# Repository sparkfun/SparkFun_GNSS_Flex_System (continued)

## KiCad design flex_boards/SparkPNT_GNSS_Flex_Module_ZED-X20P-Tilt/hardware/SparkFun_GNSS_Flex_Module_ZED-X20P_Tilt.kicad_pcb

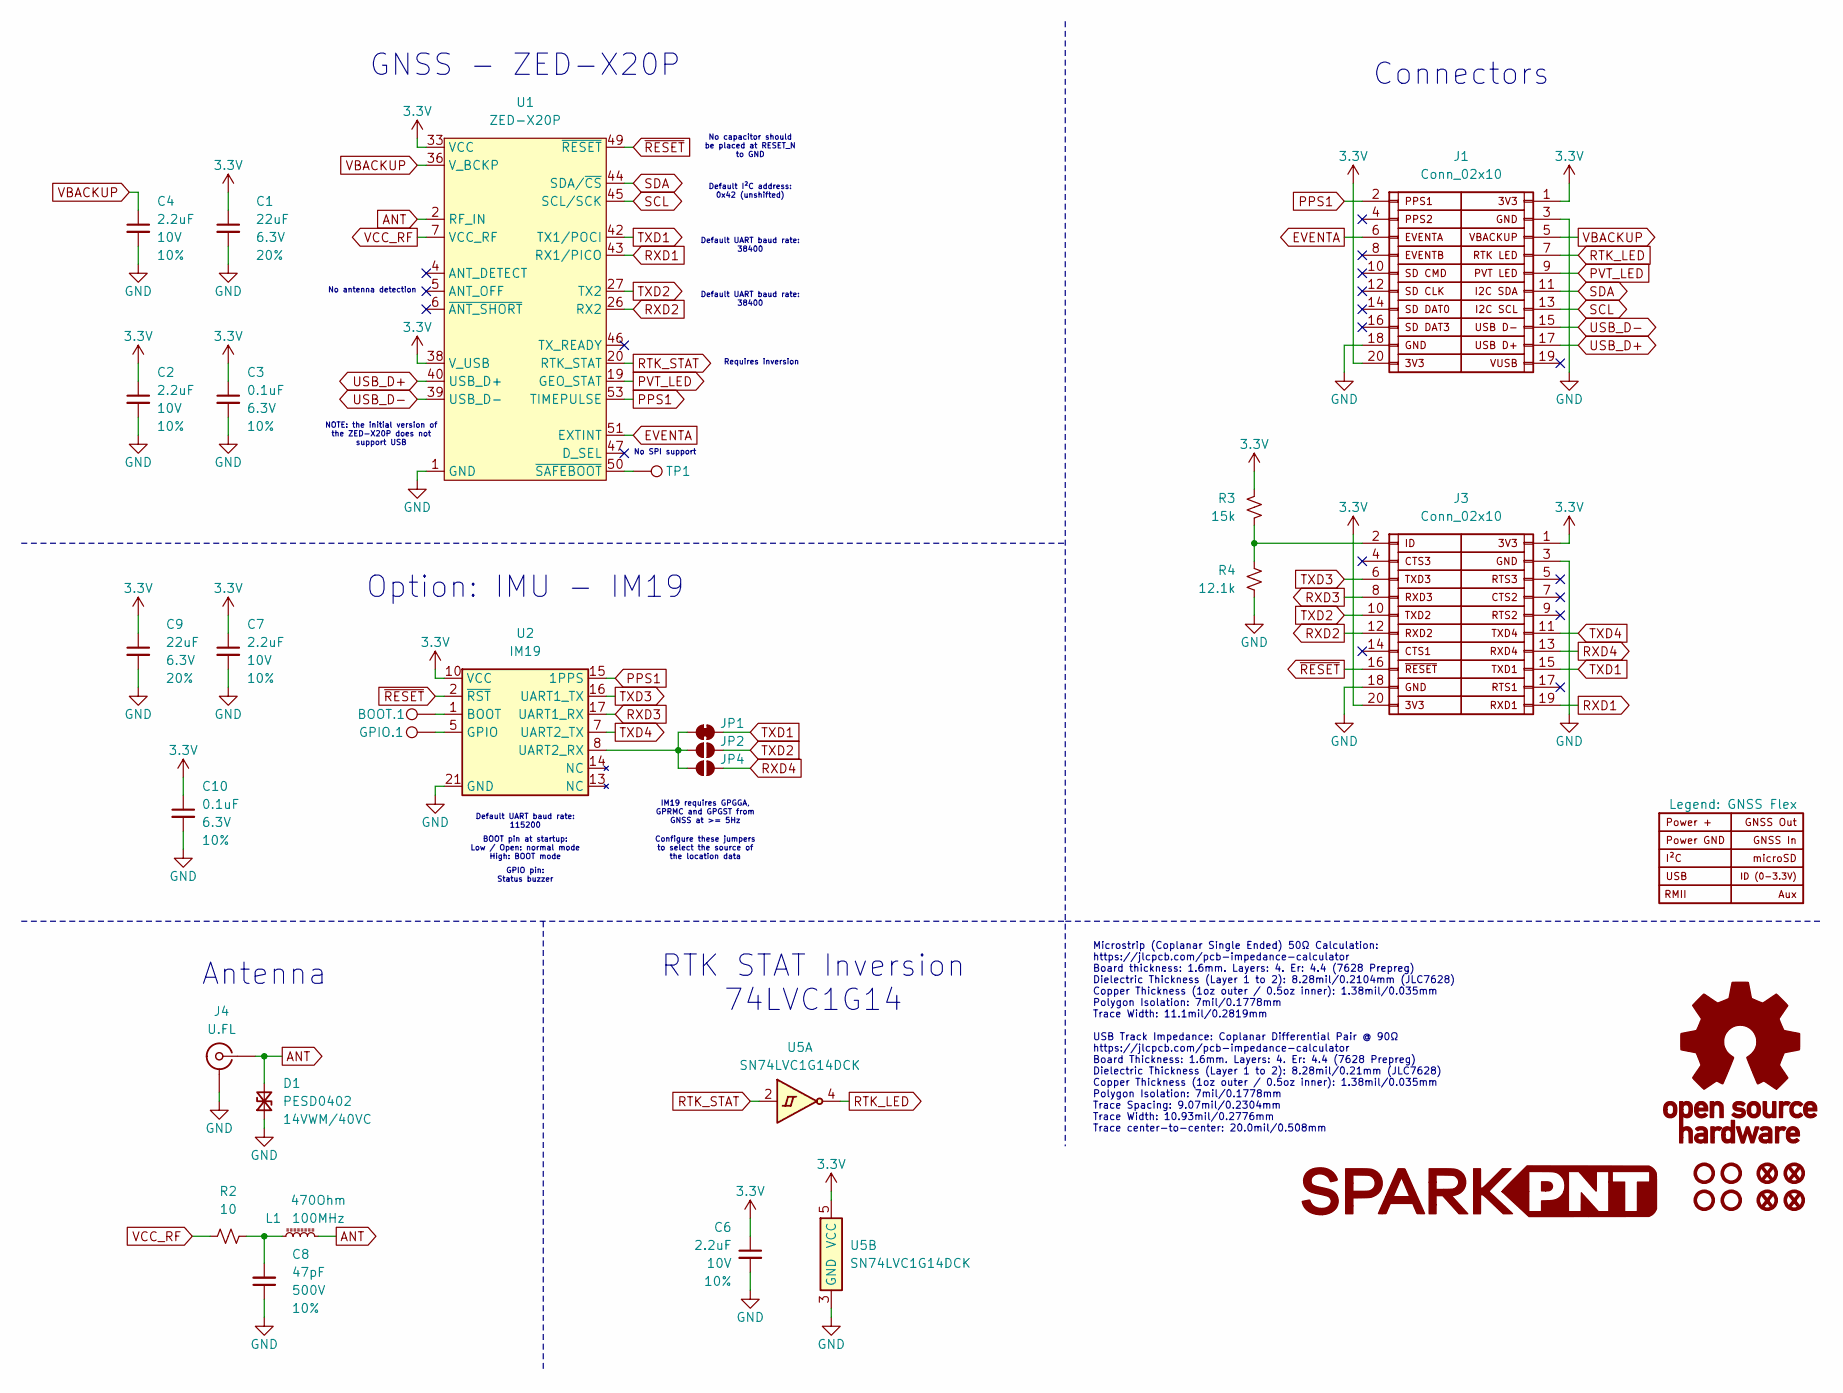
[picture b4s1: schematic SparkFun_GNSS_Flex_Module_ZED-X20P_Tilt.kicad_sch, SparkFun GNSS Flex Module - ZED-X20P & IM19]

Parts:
BOOT.1: 1.0mm; TestPoint-1.0mm
C1, C9: 22uF; C_0603_1608Metric; Voltage 6.3V; Tolerance 20%
C2, C4, C6, C7: 2.2uF; C_0402_1005Metric; Voltage 10V; Tolerance 10%
C3, C10: 0.1uF; C_0402_1005Metric; Voltage 6.3V; Tolerance 10%
C8: 47pF; C_0402_1005Metric; Voltage 500V; Tolerance 10%
D1: PESD0402; C_0402_1005Metric; Rating 14VWM/40VC
FID1, FID2, FID3, FID4: Fiducial_0.5mm; Fiducial_0.5mm_Mask1mm
G1: LOGO
G3: OSHW_Logo; Creative_Commons_License
GPIO.1: 1.0mm; TestPoint-1.0mm
J1, J3: Conn_02x10; 2x10_P2.0mm_Socket_Vertical_SMD_Pegs
J2: Legend: GNSS Flex; GNSS_Flex_Template
J4: U.FL
JP1: Jumper_2_NC_Trace
JP2, JP4: Jumper_2_NO
L1: 470Ohm; C_0603_1608Metric
R2: 10; R_0402_1005Metric
R3: 15k; R_0603_1608Metric
R4: 12.1k; R_0603_1608Metric
ST1, ST2, ST3, ST4: Standoff
TP1: 1.0mm; TestPoint-1.0mm
U1: ZED-X20P; ZED-F9P_F9T_F9R_X20P
U2: IM19
U5: SN74LVC1G14DCK; SOT-353

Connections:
3.3V: C1.1, C2.1, C3.1, C6.1, C7.1, C9.1, C10.1, J1.1, J1.20, J3.1, J3.20, R3.2, U1.33 (VCC), U1.34 (VCC), U1.38 (V_USB), U2.6 (VCC), U2.10 (VCC), U5.5 (VCC)
ANT: D1.2 (A2), J4.1 (In), L1.2, U1.2 (RF_IN)
EVENTA: J1.6, U1.51 (EXTINT)
GND: C1.2, C2.2, C3.2, C4.2, C6.2, C7.2, C8.1, C9.2, C10.2, D1.1 (A1), J1.3, J1.18, J3.3, J3.18, J4.2 (Ext), R4.1, U1.1 (GND), U1.3 (GND), U1.12 (GND), U1.14 (GND), U1.32 (GND), U1.37 (GND), U1.41 (GND), U1.48 (GND), U1.55 (GND), U1.56 (GND), U1.57 (GND), U1.58 (GND), U1.59 (GND), U1.60 (GND), U1.61 (GND), U1.62 (GND), U1.63 (GND), U1.64 (GND), U1.65 (GND), U1.66 (GND), U1.67 (GND), U1.68 (GND), U1.69 (GND), U1.70 (GND), U1.71 (GND), U1.72 (GND), U1.73 (GND), U1.74 (GND), U1.75 (GND), U1.76 (GND), U1.77 (GND), U1.78 (GND), U1.79 (GND), U1.80 (GND), U1.81 (GND), U1.82 (GND), U1.83 (GND), U1.84 (GND), U1.85 (GND), U1.86 (GND), U1.87 (GND), U1.88 (GND), U1.89 (GND), U1.90 (GND), U1.91 (GND), U1.92 (GND), U1.93 (GND), U1.94 (GND), U1.95 (GND), U1.96 (GND), U1.97 (GND), U1.98 (GND), U1.99 (GND), U1.100 (GND), U1.101 (GND), U1.102 (GND), U2.3 (GND), U2.4 (GND), U2.9 (GND), U2.18 (GND), U2.21 (GND), U5.3 (GND)
unnamed: C8.2, L1.1, R2.2
unnamed: J3.2, R3.1, R4.2
unnamed: JP1.1 (A), JP2.1 (A), JP4.1 (A), U2.8 (UART2_RX)
unnamed: TP1.1, U1.50 (~SAFEBOOT)
unnamed: BOOT.1.1, U2.1 (BOOT)
unnamed: GPIO.1.1, U2.5 (GPIO)
PPS1: J1.2, U1.53 (TIMEPULSE), U2.15 (1PPS)
PVT_LED: J1.9, U1.19 (GEO_STAT)
RTK_LED: J1.7, U5.4
RTK_STAT: U1.20 (RTK_STAT), U5.2
RXD1: J3.19, U1.43 (RX1/PICO)
RXD2: J3.12, U1.26 (RX2)
RXD3: J3.8, U2.17 (UART1_RX)
RXD4: J3.13, JP4.2 (B)
SCL: J1.13, U1.45 (SCL/SCK)
SDA: J1.11, U1.44 (SDA/~CS)
TXD1: J3.15, JP1.2 (B), U1.42 (TX1/POCI)
TXD2: J3.10, JP2.2 (B), U1.27 (TX2)
TXD3: J3.6, U2.16 (UART1_TX)
TXD4: J3.11, U2.7 (UART2_TX)
USB_D+: J1.17, U1.40 (USB_D+)
USB_D-: J1.15, U1.39 (USB_D-)
VBACKUP: C4.1, J1.5, U1.36 (V_BCKP)
VCC_RF: R2.1, U1.7 (VCC_RF)
~RESET: J3.16, U1.49 (~RESET), U2.2 (~RST)

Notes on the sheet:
Configure these jumpers to select the source of the location data
Option: IMU - IM19
IM19 requires GPGGA, GPRMC and GPGST from GNSS at >= 5Hz
Antenna
NOTE: the initial version of the ZED-X20P does not support USB
GPIO pin: Status buzzer
No antenna detection
Connectors
Default UART baud rate: 38400
Default I²C address: 0x42 (unshifted)
Requires inversion
GNSS - ZED-X20P
BOOT pin at startup: Low / Open: normal mode High: BOOT mode
No SPI support
Default UART baud rate: 115200
No capacitor should be placed at RESET_N to GND
Microstrip (Coplanar Single Ended) 50Ω Calculation: https://jlcpcb.com/pcb-impedance-calculator Board thickness: 1.6mm. Layers: 4. Er: 4.4 (7628 Prepreg) Dielectric Thickness (Layer 1 to 2): 8.28mil/0.2104mm (JLC7628) Copper Thickness (1oz outer / 0.5oz inner): 1.38mil/0.035mm Polygon Isolation: 7m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
RTK STAT Inversion 74LVC1G14

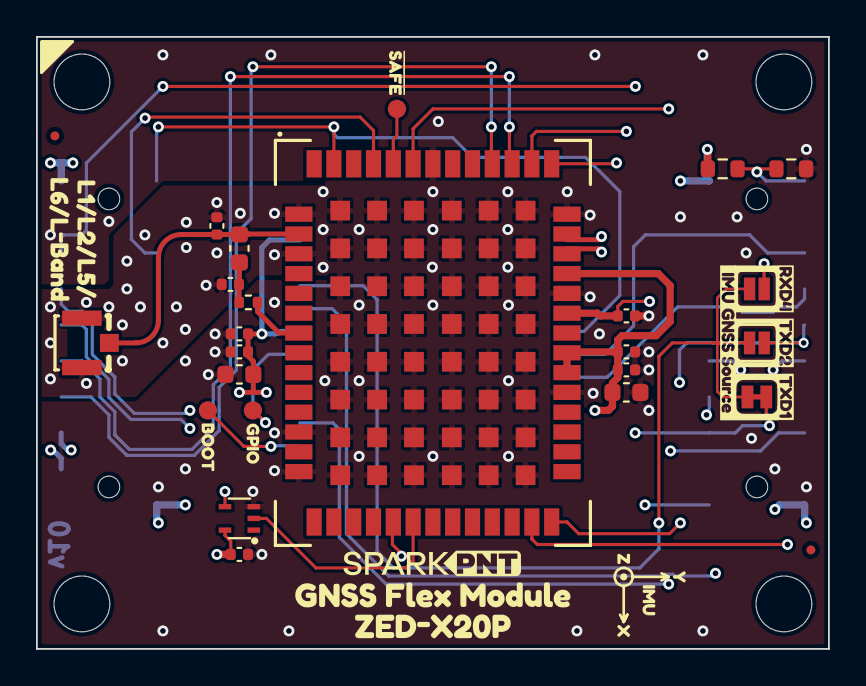
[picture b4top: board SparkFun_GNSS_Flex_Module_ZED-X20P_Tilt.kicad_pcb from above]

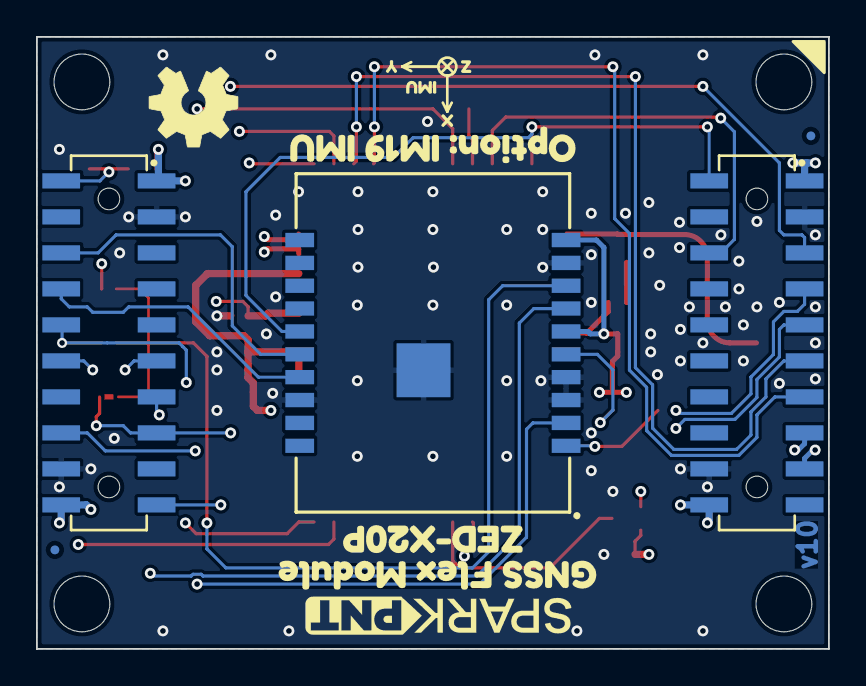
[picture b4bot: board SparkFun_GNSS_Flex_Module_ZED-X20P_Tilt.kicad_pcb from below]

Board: 4 copper layers, 44.0 x 34.0 mm, 59 parts (13 on the bottom side), 29 nets.

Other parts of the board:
Ref**: Val**; OSHW_Logo_5mm
kibuzzard-67E28C2D: G***; kibuzzard-67E28C2D
kibuzzard-67E2880B: G***; kibuzzard-67E2880B
kibuzzard-67F7F23B: G***; kibuzzard-67F7F23B
kibuzzard-67F7F255: G***; kibuzzard-67F7F255
kibuzzard-67FE65EC: G***; kibuzzard-67FE65EC
kibuzzard-67FE65FA: G***; kibuzzard-67FE65FA
kibuzzard-67FE650E: G***; kibuzzard-67FE650E
kibuzzard-67FFA928, kibuzzard-67FFA928#2: G***; kibuzzard-67FFA928
kibuzzard-67FFB45E, kibuzzard-67FFB45E#2: G***; kibuzzard-67FFB45E
kibuzzard-67FFB46A, kibuzzard-67FFB46A#2: G***; kibuzzard-67FFB46A
kibuzzard-67FFB450, kibuzzard-67FFB450#2: G***; kibuzzard-67FFB450
kibuzzard-682DAEE5: G***; kibuzzard-682DAEE5
kibuzzard-682DAFF9: G***; kibuzzard-682DAFF9
kibuzzard-682DB02A: G***; kibuzzard-682DB02A
kibuzzard-68261DE3: G***; kibuzzard-68261DE3
kibuzzard-68261E9D: G***; kibuzzard-68261E9D
kibuzzard-68261F64: G***; kibuzzard-68261F64
kibuzzard-68261F97: G***; kibuzzard-68261F97

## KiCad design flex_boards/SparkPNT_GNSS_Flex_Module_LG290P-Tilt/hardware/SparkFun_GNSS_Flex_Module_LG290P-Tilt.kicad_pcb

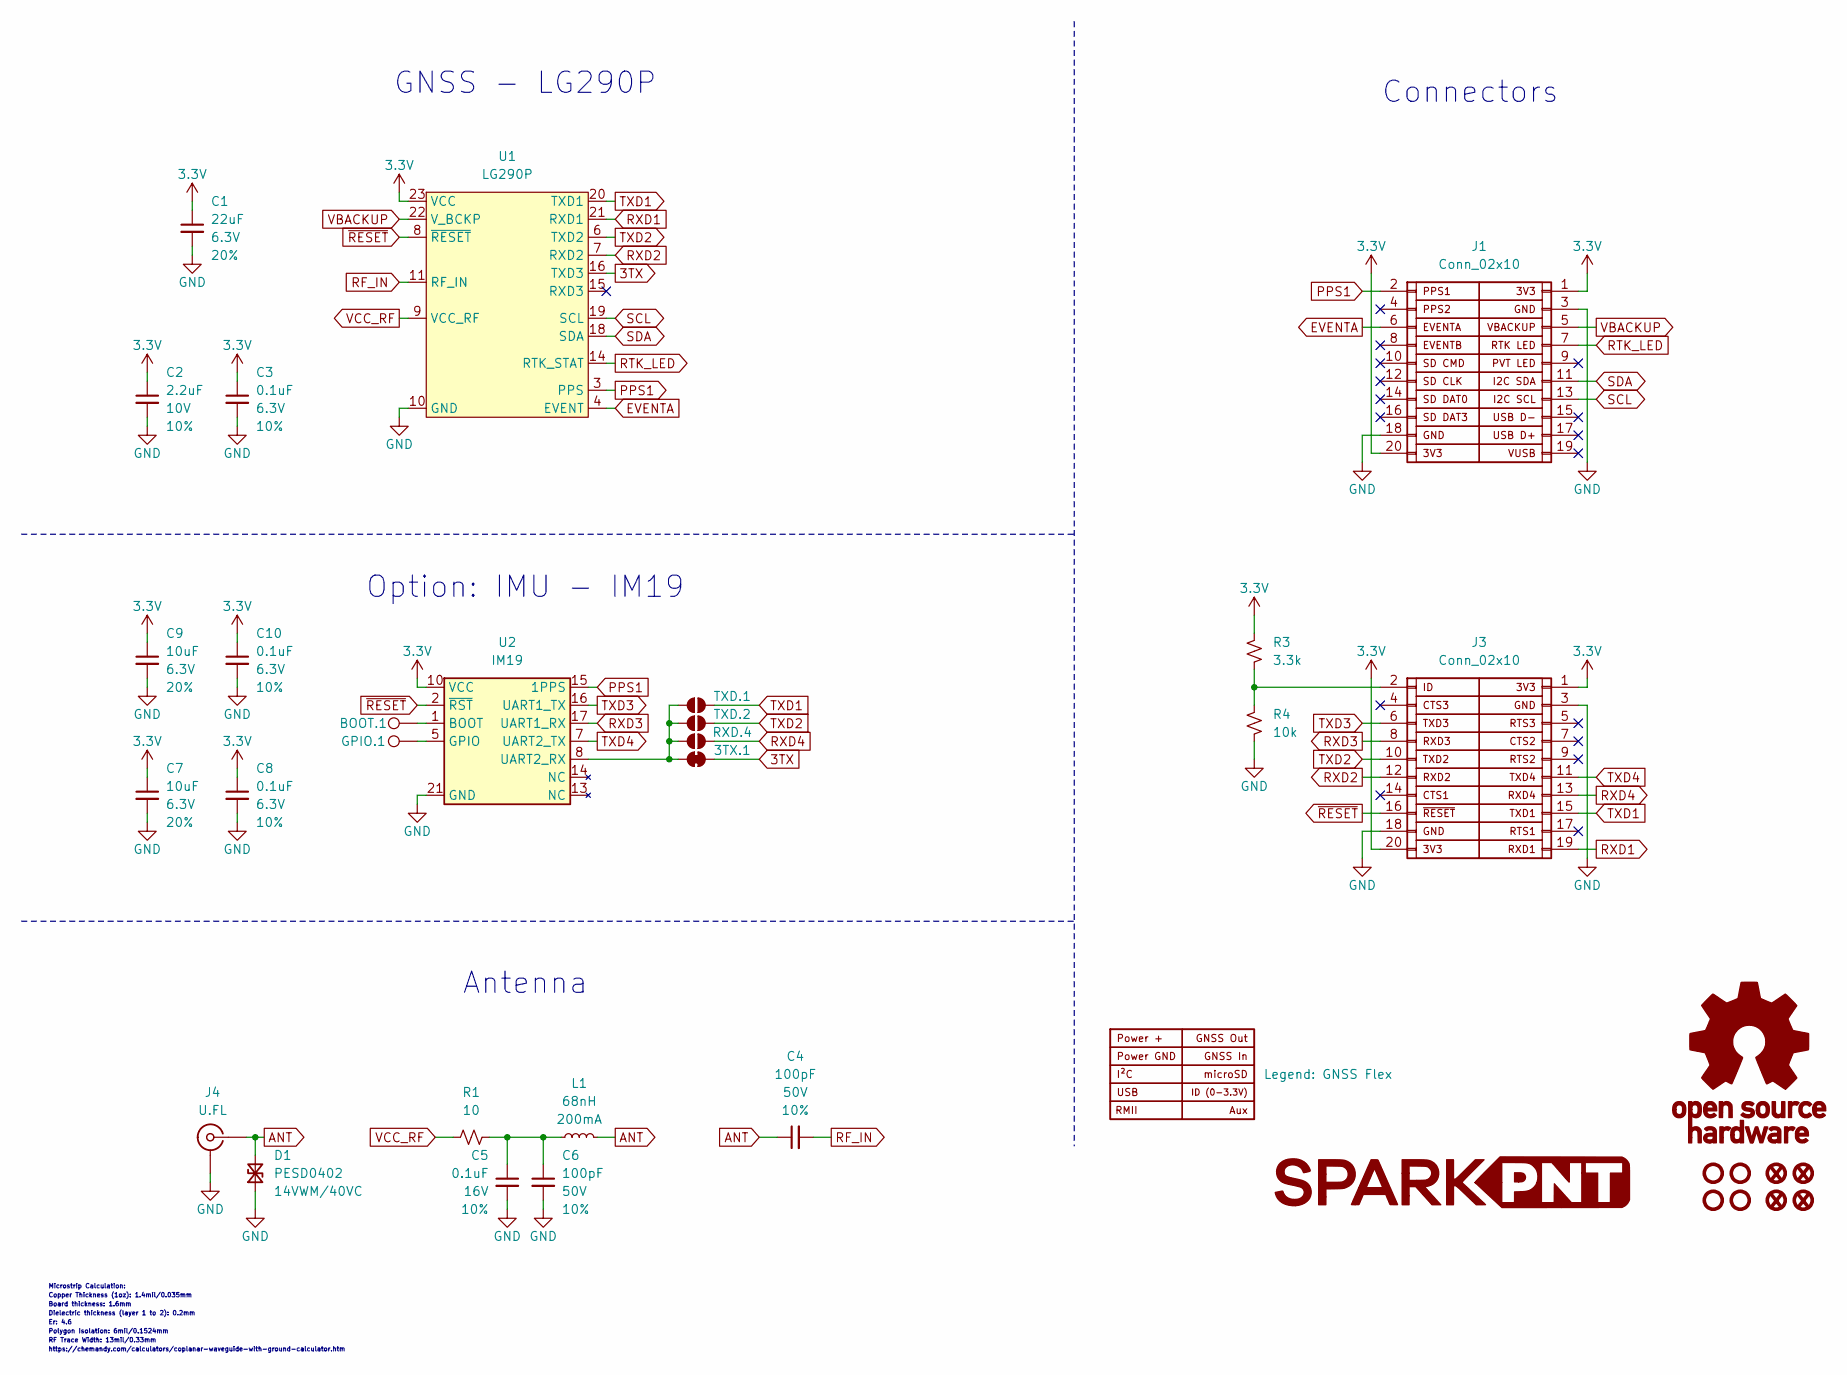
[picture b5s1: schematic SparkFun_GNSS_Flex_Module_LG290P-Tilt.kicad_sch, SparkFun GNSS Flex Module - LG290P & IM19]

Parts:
3TX.1: Jumper_2_NC_Trace
BOOT.1: 1.0mm; TestPoint-1.0mm
C1: 22uF; C_0603_1608Metric; Voltage 6.3V; Tolerance 20%
C2: 2.2uF; C_0402_1005Metric; Voltage 10V; Tolerance 10%
C3, C8, C10: 0.1uF; C_0402_1005Metric; Voltage 6.3V; Tolerance 10%
C4, C6: 100pF; C_0402_1005Metric; Voltage 50V; Tolerance 10%
C5: 0.1uF; C_0402_1005Metric; Voltage 16V; Tolerance 10%
C7, C9: 10uF; C_0603_1608Metric; Voltage 6.3V; Tolerance 20%
D1: PESD0402; C_0402_1005Metric; Rating 14VWM/40VC
FID1, FID2, FID3, FID4: Fiducial_0.5mm; Fiducial_0.5mm_Mask1mm
G1: LOGO
G3: OSHW_Logo; Creative_Commons_License
GPIO.1: 1.0mm; TestPoint-1.0mm
J1, J3: Conn_02x10; 2x10_P2.0mm_Socket_Vertical_SMD_Pegs
J2: Legend: GNSS Flex; GNSS_Flex_Template
J4: U.FL
L1: 68nH; C_0402_1005Metric
R1: 10; R_0402_1005Metric
R3: 3.3k; R_0603_1608Metric
R4: 10k; R_0603_1608Metric
RXD.4: Jumper_2_NO
ST1, ST2, ST3, ST4: Standoff
TXD.1, TXD.2: Jumper_2_NO
U1: LG290P; Quectel_LG290P
U2: IM19

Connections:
3.3V: C1.1, C2.1, C3.1, C7.1, C8.1, C9.1, C10.1, J1.1, J1.20, J3.1, J3.20, R3.2, U1.23 (VCC), U2.6 (VCC), U2.10 (VCC)
3TX: 3TX.1.2 (B), U1.16 (TXD3)
ANT: C4.1, D1.2 (A2), J4.1 (In), L1.2
EVENTA: J1.6, U1.4 (EVENT)
GND: C1.2, C2.2, C3.2, C5.2, C6.2, C7.2, C8.2, C9.2, C10.2, D1.1 (A1), J1.3, J1.18, J3.3, J3.18, J4.2 (Ext), R4.1, U1.10 (GND), U1.12 (GND), U1.13 (GND), U1.24 (GND), U1.25 (GND), U2.3 (GND), U2.4 (GND), U2.9 (GND), U2.18 (GND), U2.21 (GND)
unnamed: 3TX.1.1 (A), RXD.4.1 (A), TXD.1.1 (A), TXD.2.1 (A), U2.8 (UART2_RX)
unnamed: C5.1, C6.1, L1.1, R1.2
unnamed: J3.2, R3.1, R4.2
unnamed: BOOT.1.1, U2.1 (BOOT)
unnamed: GPIO.1.1, U2.5 (GPIO)
PPS1: J1.2, U1.3 (PPS), U2.15 (1PPS)
RF_IN: C4.2, U1.11 (RF_IN)
RTK_LED: J1.7, U1.14 (RTK_STAT)
RXD1: J3.19, U1.21 (RXD1)
RXD2: J3.12, U1.7 (RXD2)
RXD3: J3.8, U2.17 (UART1_RX)
RXD4: J3.13, RXD.4.2 (B)
SCL: J1.13, U1.19 (SCL)
SDA: J1.11, U1.18 (SDA)
TXD1: J3.15, TXD.1.2 (B), U1.20 (TXD1)
TXD2: J3.10, TXD.2.2 (B), U1.6 (TXD2)
TXD3: J3.6, U2.16 (UART1_TX)
TXD4: J3.11, U2.7 (UART2_TX)
VBACKUP: J1.5, U1.22 (V_BCKP)
VCC_RF: R1.1, U1.9 (VCC_RF)
~RESET: J3.16, U1.8 (~RESET), U2.2 (~RST)

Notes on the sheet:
Copper Thickness (1oz): 1.4mil/0.035mm
Board thickness: 1.6mm
Er: 4.6
Antenna
Option: IMU - IM19
Connectors
GNSS - LG290P
https://chemandy.com/calculators/coplanar-waveguide-with-ground-calculator.htm
Microstrip Calculation:
Polygon Isolation: 6mil/0.1524mm
Dielectric thickness (layer 1 to 2): 0.2mm
RF Trace Width: 13mil/0.33mm

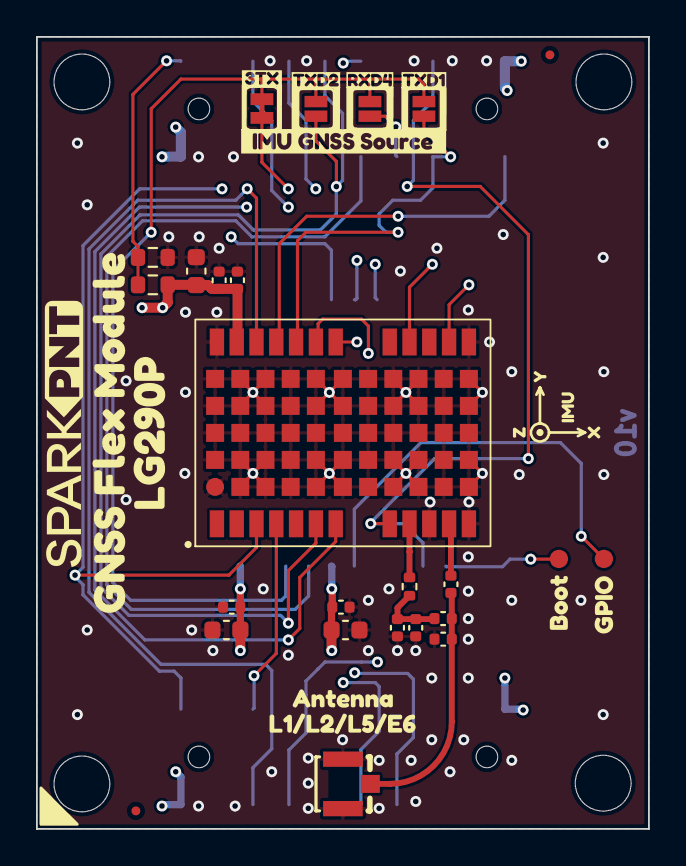
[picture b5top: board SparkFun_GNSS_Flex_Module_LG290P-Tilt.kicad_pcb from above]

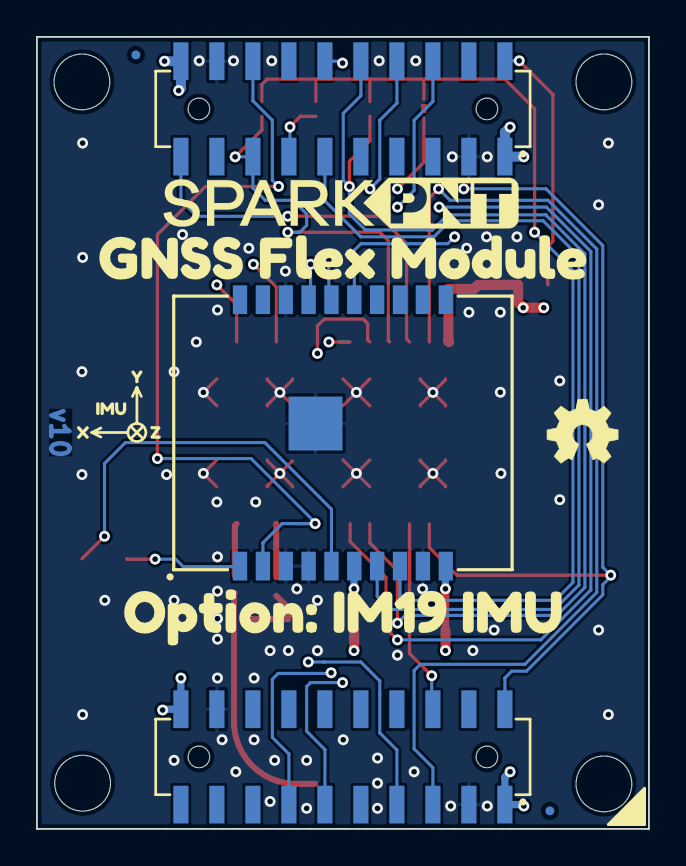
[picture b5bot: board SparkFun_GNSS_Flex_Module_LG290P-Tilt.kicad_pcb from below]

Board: 4 copper layers, 34.0 x 44.0 mm, 58 parts (12 on the bottom side), 26 nets.

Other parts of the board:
Ref**: Val**; OSHW_Logo_4mm
kibuzzard-67DC4CF4: G***; kibuzzard-67DC4CF4
kibuzzard-67DC4D0C: G***; kibuzzard-67DC4D0C
kibuzzard-67FFA928, kibuzzard-67FFA928#2: G***; kibuzzard-67FFA928
kibuzzard-67FFB45E, kibuzzard-67FFB45E#2: G***; kibuzzard-67FFB45E
kibuzzard-67FFB46A, kibuzzard-67FFB46A#2: G***; kibuzzard-67FFB46A
kibuzzard-67FFB450, kibuzzard-67FFB450#2: G***; kibuzzard-67FFB450
kibuzzard-679B60B6: G***; kibuzzard-679B60B6
kibuzzard-684984CE: G***; kibuzzard-684984CE
kibuzzard-684984F2: G***; kibuzzard-684984F2
kibuzzard-6849609B: G***; kibuzzard-6849609B
kibuzzard-6849850D: G***; kibuzzard-6849850D
kibuzzard-67975357: G***; kibuzzard-67975357
kibuzzard-67975369: G***; kibuzzard-67975369
kibuzzard-68496623: G***; kibuzzard-68496623
kibuzzard-68496634: G***; kibuzzard-68496634
kibuzzard-68498826: G***; kibuzzard-68498826
kibuzzard-68498864: G***; kibuzzard-68498864

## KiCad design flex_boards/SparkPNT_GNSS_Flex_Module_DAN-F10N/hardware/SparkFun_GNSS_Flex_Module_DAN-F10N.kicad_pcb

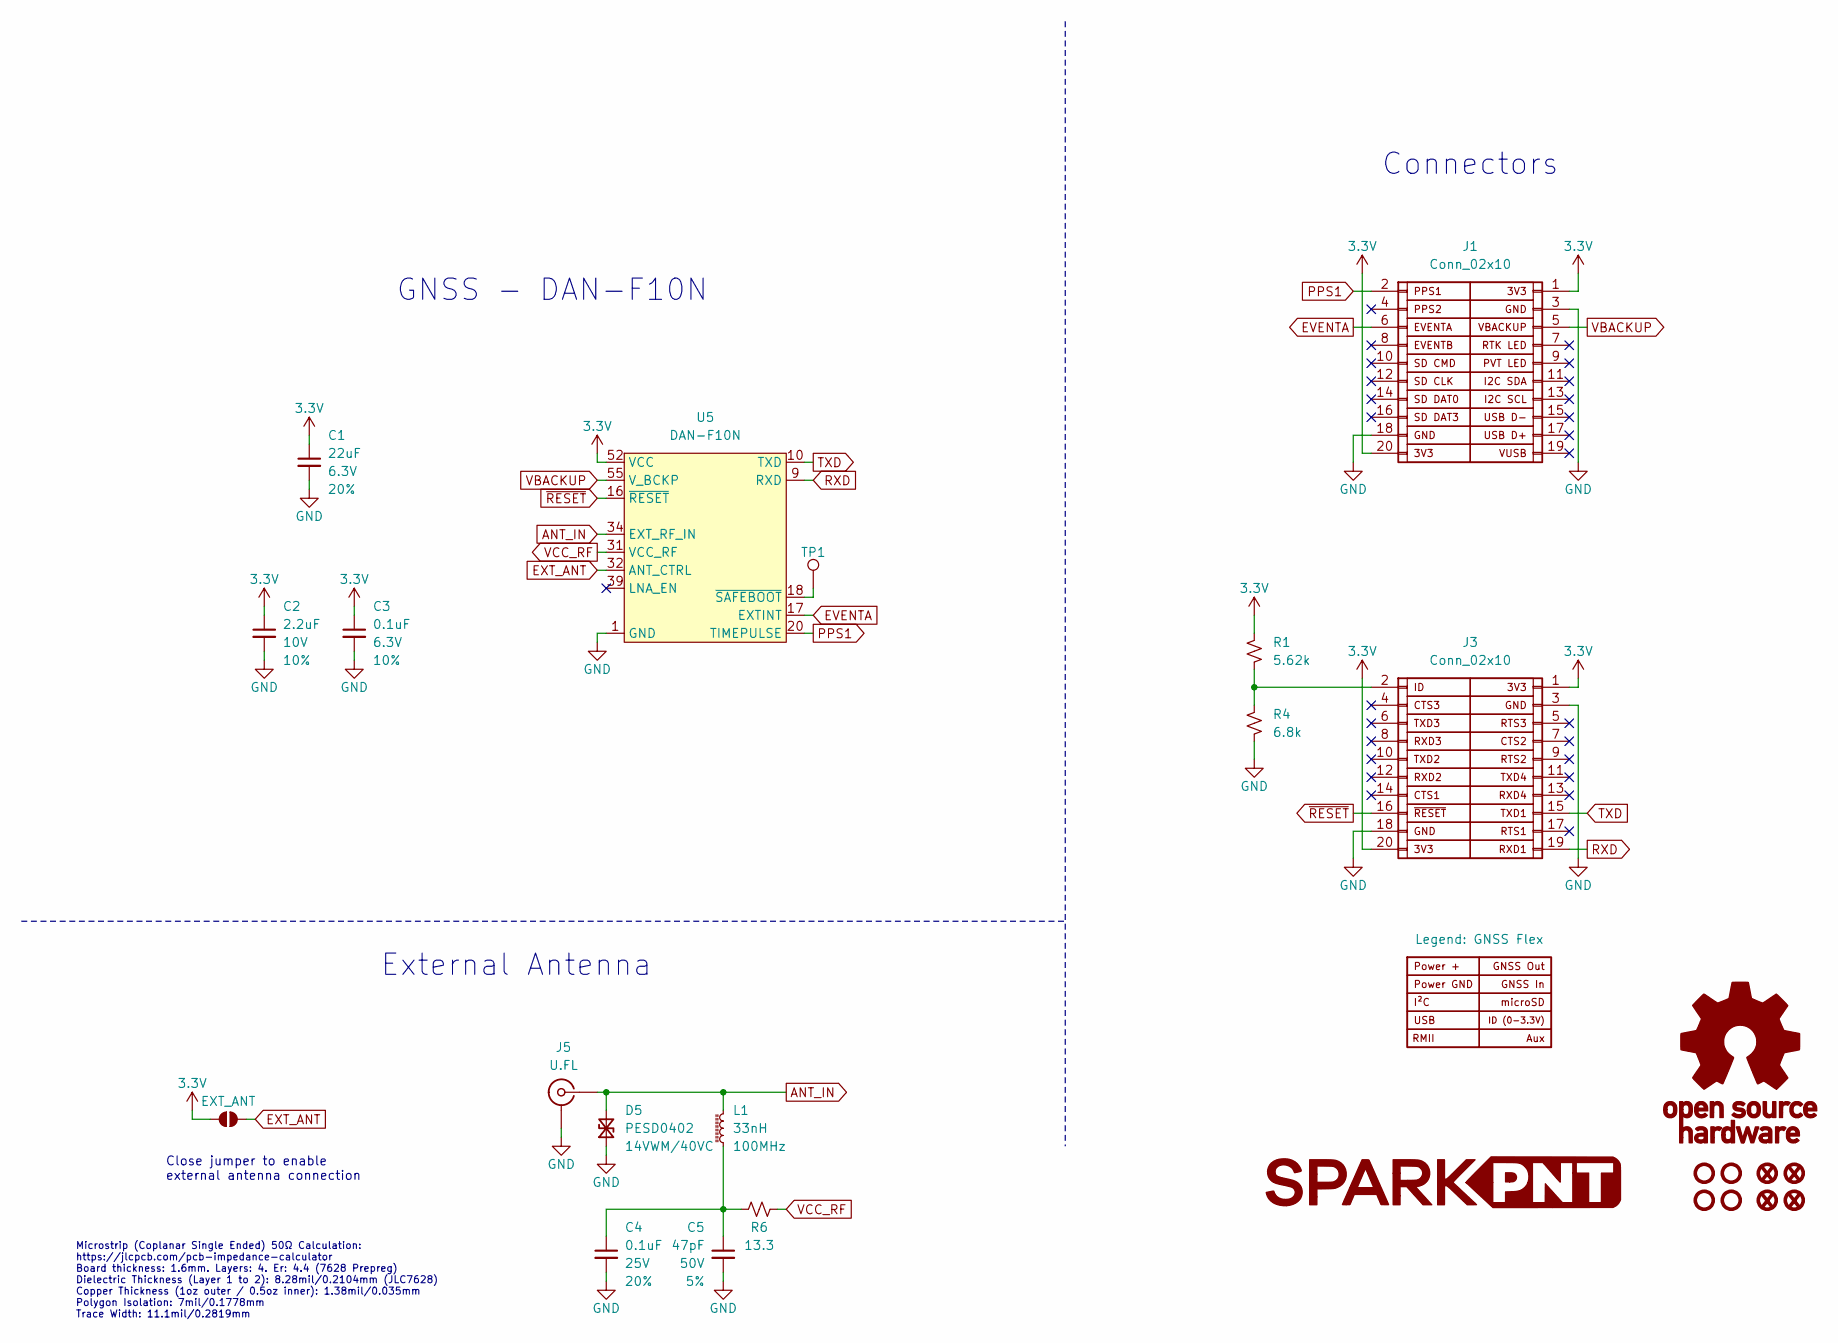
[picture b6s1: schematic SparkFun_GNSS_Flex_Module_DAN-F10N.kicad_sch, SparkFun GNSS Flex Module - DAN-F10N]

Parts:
C1: 22uF; C_0603_1608Metric; Voltage 6.3V; Tolerance 20%
C2: 2.2uF; C_0402_1005Metric; Voltage 10V; Tolerance 10%
C3: 0.1uF; C_0402_1005Metric; Voltage 6.3V; Tolerance 10%
C4: 0.1uF; C_0603_1608Metric; Voltage 25V; Tolerance 20%
C5: 47pF; C_0603_1608Metric; Voltage 50V; Tolerance 5%
D5: PESD0402; C_0402_1005Metric; Rating 14VWM/40VC
FID1, FID2, FID3, FID4: Fiducial_0.5mm; Fiducial_0.5mm_Mask1mm
G1: LOGO
G3: OSHW_Logo; Creative_Commons_License
J1, J3: Conn_02x10; 2x10_2.0mm_Female_Socket_Vertical_SMD_Pegs
J2: Legend: GNSS Flex; GNSS_Flex_Template
J5: U.FL
JP1: EXT_ANT; Jumper_2_NO
L1: 33nH; C_0603_1608Metric
R1: 5.62k; R_0603_1608Metric
R4: 6.8k; R_0603_1608Metric
R6: 13.3; R_2512_6332Metric
ST1, ST2, ST3, ST4: Standoff
TP1: 1.0mm; TestPoint-1.0mm
U5: DAN-F10N

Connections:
3.3V: C1.1, C2.1, C3.1, J1.1, J1.20, J3.1, J3.20, JP1.1 (A), R1.2, U5.52 (VCC), U5.53 (VCC)
ANT_IN: D5.2 (A2), J5.1 (In), L1.2, U5.34 (EXT_RF_IN)
EVENTA: J1.6, U5.17 (EXTINT)
EXT_ANT: JP1.2 (B), U5.32 (ANT_CTRL)
GND: C1.2, C2.2, C3.2, C4.2, C5.2, D5.1 (A1), J1.3, J1.18, J3.3, J3.18, J5.2 (Ext), R4.1, U5.1 (GND), U5.2 (GND), U5.3 (GND), U5.4 (GND), U5.5 (GND), U5.6 (GND), U5.7 (GND), U5.8 (GND), U5.13 (GND), U5.14 (GND), U5.15 (GND), U5.19 (GND), U5.21 (GND), U5.22 (GND), U5.23 (GND), U5.26 (GND), U5.27 (GND), U5.28 (GND), U5.29 (GND), U5.30 (GND), U5.33 (GND), U5.35 (GND), U5.37 (GND), U5.38 (GND), U5.40 (GND), U5.41 (GND), U5.42 (GND), U5.43 (GND), U5.44 (GND), U5.47 (GND), U5.48 (GND), U5.49 (GND), U5.50 (GND), U5.51 (GND), U5.54 (GND), U5.56 (GND), U5.57 (GND)
unnamed: C4.1, C5.1, L1.1, R6.2
unnamed: J3.2, R1.1, R4.2
unnamed: TP1.1, U5.18 (~SAFEBOOT)
PPS1: J1.2, U5.20 (TIMEPULSE)
RXD: J3.19, U5.9 (RXD)
TXD: J3.15, U5.10 (TXD)
VBACKUP: J1.5, U5.55 (V_BCKP)
VCC_RF: R6.1, U5.31 (VCC_RF)
~RESET: J3.16, U5.16 (~RESET)

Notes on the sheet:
External Antenna
Connectors
GNSS - DAN-F10N
Close jumper to enable external antenna connection
Microstrip (Coplanar Single Ended) 50Ω Calculation: https://jlcpcb.com/pcb-impedance-calculator Board thickness: 1.6mm. Layers: 4. Er: 4.4 (7628 Prepreg) Dielectric Thickness (Layer 1 to 2): 8.28mil/0.2104mm (JLC7628) Copper Thickness (1oz outer / 0.5oz inner): 1.38mil/0.035mm Polygon Isolation: 7m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

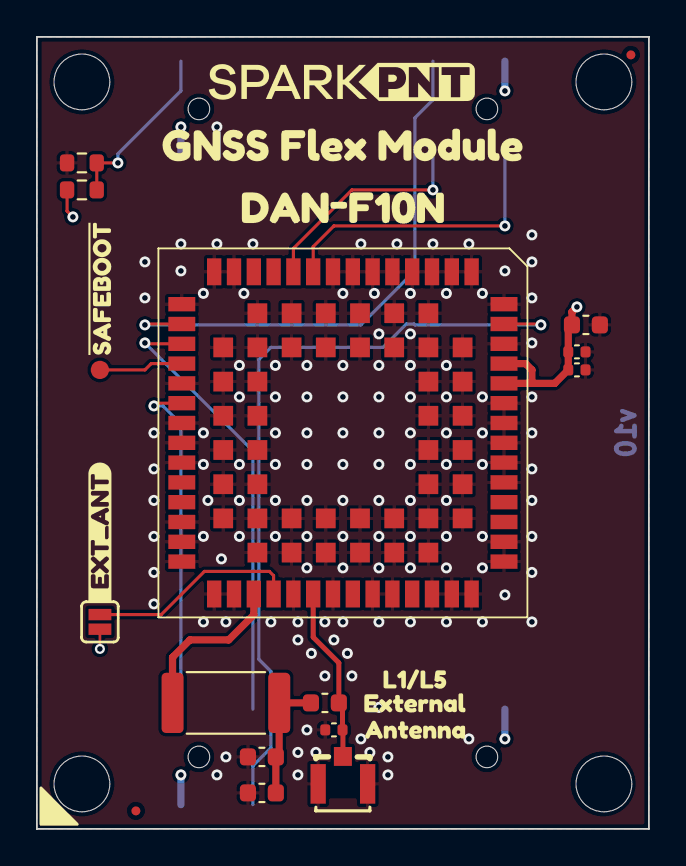
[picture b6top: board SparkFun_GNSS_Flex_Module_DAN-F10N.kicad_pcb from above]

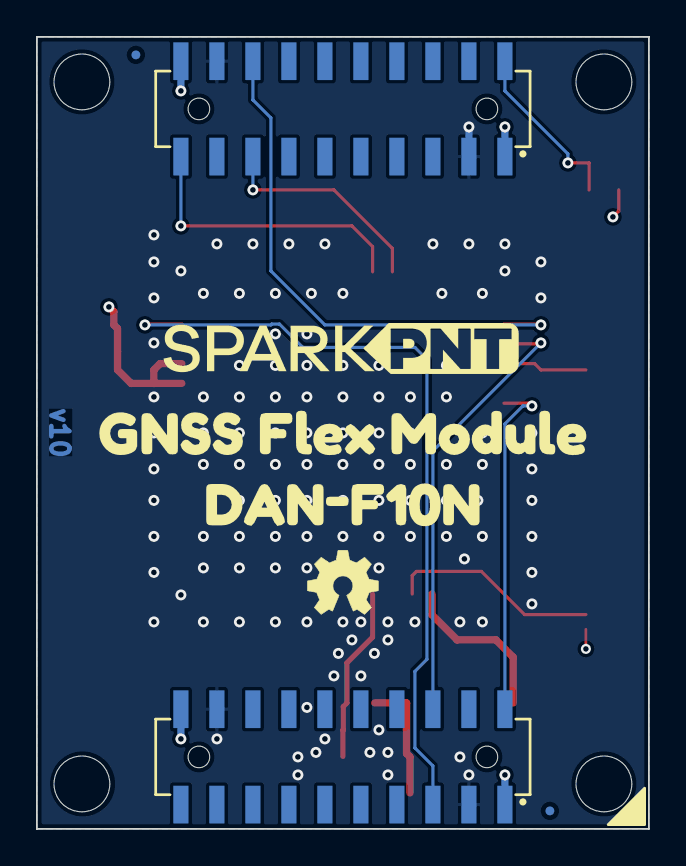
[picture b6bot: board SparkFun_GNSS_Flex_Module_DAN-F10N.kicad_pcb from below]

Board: 4 copper layers, 34.0 x 44.0 mm, 36 parts (7 on the bottom side), 14 nets.

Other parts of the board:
Ref**: Val**; OSHW_Logo_4mm
kibuzzard-67DC4CF4: G***; kibuzzard-67DC4CF4
kibuzzard-67DC4D0C: G***; kibuzzard-67DC4D0C
kibuzzard-67F5D276: G***; kibuzzard-67F5D276
kibuzzard-67F49BA9: G***; kibuzzard-67F49BA9
kibuzzard-67F49BB0: G***; kibuzzard-67F49BB0
kibuzzard-67F49BC0: G***; kibuzzard-67F49BC0
kibuzzard-67FE95EA: G***; kibuzzard-67FE95EA
kibuzzard-67FE959B: G***; kibuzzard-67FE959B
kibuzzard-67975369: G***; kibuzzard-67975369

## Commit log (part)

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2025-04-29 Remove directories
2025-04-29 Update template files
2025-05-15 Initial Draft - Flex System
2025-05-15 Initial Draft - mosaic-X5
2025-05-16 Update - mosaic-X5
    - Adds QR codes for videos
    - Fix typos
2025-05-16 Update - Flex System
    - Fix link
2025-05-16 Add build workflow
    Add workflow to build documentation for GitHub Pages
2025-05-16 Deployed fa99f3e with MkDocs version: 1.6.1
2025-05-16 Remove file
2025-05-16 Deployed a7084e1 with MkDocs version: 1.6.1
2025-05-16 Deployed c31044d with MkDocs version: 1.6.1
2025-05-16 Manually add pHAT Files
2025-05-16 Deployed fc5b3ee with MkDocs version: 1.6.1
2025-05-19 Minor corrections
2025-05-19 Correct X5 grid
2025-05-19 Correct image link
2025-05-19 Fix path to pHAT files
2025-05-19 Tweaks
2025-05-20 Remove pHAT files
2025-05-20 Update mkdocs config
2025-05-20 Update build workflow
2025-05-20 Update submodule
2025-05-20 Fix redirect
2025-05-20 Replace center tag
    Replace the use of `<center>` tag for deprecation, as described in issue: https://github.com/squidfunk/mkdocs-material/issues/8163
2025-05-20 Fix pHAT resources links
2025-05-20 Clarify ecosystem examples
2025-05-21 Replace center tag
    Replace `<center>` tag
2025-05-21 Fix banner title
    Update from SparkFun to SparkPNT
2025-05-21 Embed color adjustment script
    The color adjustment script for the 3D models is now automatically built into the documentation and doesn't need to to be declared every time
2025-05-21 Update interfaces information
2025-05-21 Add board stacking animation
    Animation working, needed to declare `autoplay` attribute
2025-05-21 Update modules section
    Add landing page for modules
    Add product links for each module
    Add hookup guide banner
2025-05-21 Add landing page for carrier boards
2025-05-21 Update system_overview.md
    Changed header to Board Variants
    Resized models
    Revised Ecosystem Boards section to list all Flex boards
2025-05-21 Update system_overview.md
    Fix headers
2025-05-21 Remove redundant images
2025-05-21 Change file name
    Use same naming convention as LG290P guide
2025-05-21 Fix video margin
    From center tag replacement
2025-05-22 Update kicad_files.zip
    Add project file
2025-05-22 Deployed bb9bfb6 with MkDocs version: 1.6.1
2025-07-03 Add issue workflow
    Test workflow for @gigapod
    Workflow will append issue to project folder
2025-08-20 Reconfigure homepage
    Re-establish homepage link to the landing page for the current website; instead of redirecting to sparkfun.com
    Follows standard practice
2025-08-20 Improve CSS and page layout
    - Fix QR code for product links
    - Fix QR code for videos
    - Use grid layout to improve page layout
    - Remove navigation buttons from footer
    - Styling updates
2025-08-20 Update mosaic-X5
    Add instructions for enabling specific GNSS signals/sats
2025-08-20 Update Generic 3D Models
    Update files with more optimized versions
2025-08-20 Add images for Qwiic Connector System
    Add logos and QR code for video
2025-08-20 Update mosaic-X5
    Add images (unused)
2025-08-20 Update README.md
    Fix release number; forgot to generate the initial release
2025-08-20 Update README
    Clarified that 'module-pinout.png' now includes the alignment marker and removed the separate entry for 'module-pinout2.png'.
2025-08-20 Template for New GNSS Flex Modules
    Introduces initial documentation structure, image assets, and configuration files for SparkPNT GNSS Flex Modules. Includes README files for asset directories, banner images, initial image templates f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
2025-08-21 Add DAN-F10N GNSS Flex module
    Add the u-blox DAN-F10N GNSS Flex module to the GNSS Flex system documentation
2025-08-21 Add u-center 2 software
    Add information for u-center 2 software, which supports u-blox GNSS modules
2025-08-21 Update docs
    Updated links to SparkFun forum
    Standardized QR code image sizes
2025-08-21 Update antenna information
    Replaced references of "GPS" with "GNSS"
    Add recommendation to have a clear view of the sky
2025-08-21 Update README
    Fixed minor grammatical issues
2025-08-21 Update software_overview.md
    Add alt text
2025-08-23 Update antenna information
    Replaced reference of "GPS" with "GNSS"
2025-08-23 Update mkdocs.yml
    Added navigation.instant, navigation.instant.prefetch, and navigation.instant.progress features to improve page load time
    Enabled announce.dismiss feature to allow users to dismiss the announcement bar
2025-08-23 Update icons
    Add icons for Hexagon (acquired Septentrio)
2025-09-04 Update docs
    Changed the tooltip text from 'Click download' to 'Click to download' in hardware_overview.md for DAN-F10N, LG290P, and mosaic-X5 modules for improved clarity.
2025-09-04 Update docs formatting
    Replaced HTML superscript tags with Markdown-style caret notation for I2C references
2025-09-04 Update poster images for GNSS Flex Modules
    Add/updated poster images for the 3D models of the GNSS Flex modules
2025-09-04 Update docs for 3D models
    Removed commented-out banner images and adjusted QR code image classes in modules documentation. Updated grid styling and include references in system overview documentation for improved layout and c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
2025-09-04 Deployed 15da8b3 with MkDocs version: 1.6.1
2025-09-08 Deployed f3a74ea with MkDocs version: 1.6.1
2025-09-08 Consolidate <figcaption> elements
    Converted multi-line <figcaption> elements into a single-line format
2025-09-08 Update docs
    Added tips for GNSS antenna use
    Clarified voltage injection information
    Updated arduino_library.png image
2025-09-09 Add GNSS Flex module docs - LG290P & IMU
    Files to add a hookup guide for the SparkPNT GNSS Flex Module - LG290P & IMU
2025-09-09 Add new GNSS Flex modules to docs
    Update product listings and resources
    Expanded documentation to include the new GNSS Flex modules:
    - ZED-X20P with optional IMU
    - LG290P with IMU
2025-09-09 Add IM19 Attitude Module to docs
    Added a new documentation page for the IM19 Attitude Module, including technical details, configuration instructions, and software resources. Added related images and diagrams to the assets directory.
    Updated `mkdocs.yml` to include the new documentation under Applications > Tilt Compensation.
2025-09-09 Deployed cb8bac0 with MkDocs version: 1.6.1
2025-09-09 Update KiCAD files
    Files with update footprint paths and orientation
2025-09-09 Deployed da65b15 with MkDocs version: 1.6.1
2025-09-09 Remove products
    Remove unused product links and resources
2025-09-10 Update .gitignore
    Remove leftover merge conflict markers
    Consolidate duplicate entries
2025-09-10 Update .gitmodules
    Changed the SparkFun_GNSS_Flex_pHAT submodule URL from SSH to HTTPS for compatibility
2025-09-10 Deployed ab3a2ff with MkDocs version: 1.6.1
2025-09-12 Update KiCAD files
    Update the file paths for the 3D model footprints
2025-09-15 Update component documentation
    Updates the datasheet, firmware, manuals, etc. for the LG290P GNSS Flex module
2025-09-15 Update component documentation
    Updates the datasheet, firmware, manuals, etc. for the LG290P + IM19 GNSS Flex module
2025-09-16 Add GNSS Flex Breakout
    Adds https://github.com/sparkfun/SparkFun_GNSS_Flex_Breakout as a submodule
2025-09-16 Add GNSS Flex breakout to docs
2025-09-16 Update docs
    Update releases
    Link GNSS Flex breakout into system overview
    Replace <center> and <sup> tags
    Fix links
    Add instructional video
    Update antenna and software instructions
2025-09-18 Deployed f1a8126 with MkDocs version: 1.6.1
2025-10-10 Add GNSS Flex module docs - LG580P
    Files to add a hookup guide for the SparkPNT GNSS Flex Module - LG580P
2025-10-10 Add GNSS Flex module to docs
    Update product listings and resources
    Expanded documentation to include the LG580P GNSS Flex module
2025-10-10 Update resources.md
    - Removed software link on DAN-F10
    - Reorganized the LG290P component documentation file to be consistent
2025-10-10 Standardize names
    Updated section titles to use 'GNSS Receiver'
    Standardized naming convention of ZED-X20P module
2025-10-10 Move images to `templates-old` folder
    Moved image files to the templates-old subdirectory to separate of legacy files
2025-10-10 Fix links
    Update product links for SEO
2025-10-10 Add SparkPNT GNSS Flex logo
    Adds the GNSS Flex logo to the `overrides/.icon` directory
2025-10-10 Update workflows
    Use requirements.txt to install dependencies
    Adds new workflow that uses the sparse checkout attribute to reduce the build time
2025-10-10 Update 3D models
    Refactored the 3D models for all the GNSS Flex boards to a new standardization
    Eliminated the manual adjustments required for any new 3D models
    - Modified the old models, so any new models can be adopted without any changes after they have been optimized
2025-10-10 Update GNSS Headers section of all Quectel boards
    Standardized the GNSS Header section layout
    Updated the UART protocol information
    - Adds the QGC protocol support details and message lists
    - Adds the qgc_protocol.png image
    - Updated UART protocol sections to include the expanded message types
2025-10-10 Change hompage link
    Redirects the link for homepage icon to the GNS Flex modules page
2025-10-10 Update README.md
    Added entry for r2025-10 release, which introduces the LG580P GNSS Flex module and documentation updates.
2025-10-10 Add icons to titles
2025-10-10 Add image for reset pin
2025-10-10 Update hardware_overview.md
    Fix link
2025-10-10 Deployed 5fe8a15 with MkDocs version: 1.6.1
2025-10-17 Add GNSS Flex module docs - mosaic-X5 & IM19
    Files to add a hookup guide for the SparkPNT GNSS Flex Module - mosaic-X5 & IM19
2025-10-30 Standardize GNSS receiver
    Standardize use of GNSS receiver instead of GNSS module to avoid ambiguity with references to the GNSS Flex module
2025-10-30 Update forum link
2025-10-30 Standardize product description
    Standardize product description to include overview of GNSS Flex modules and available interfaces
2025-10-30 Fix grammar
    Adds Oxford comma
2025-10-30 Update ESD banner
    Remove erroneous info from copy/paste
    Remove product link
2025-10-30 Update generic models
    Fixes render of material layers
2025-10-30 Fix rotation
    Fixes rotation direction
2025-10-30 Update README.md
    Fix spacing for Markdown linting
2025-10-30 Move Firmware Files
    Moves the HPG 2.00 firmware files into their own directory
2025-11-04 Adds New Firmware
    Adds the HPG 2.02 firmware files into their own directory
    Update links in `resources.md`
2025-11-04 Add documentation
    Adds documentation for the firmware update process
2025-11-04 Update releases
2025-11-04 Fix link
2026-02-25 Docs - G5 Update
    Adds docs for moasic-G5 P3 Flex modules
2026-02-25 Docs - Tech Assist Update
    Removed links to technical assistance webpage (404 retail site)
    - Removed or relocated???
2026-02-25 Docs - Updates
    Fiexs typos, links, missing info and files
2026-02-25 Build Fix
    Update hyperlink for Septentrio image
2026-02-25 Deployed 816213a with MkDocs version: 1.6.1
2026-03-25 Add KiCad files
    Adds KiCad files to the /hardware and /hardware/production directories of each GNSS Flex module
2026-03-25 Update repository contents
    Updates the file directory for the repository
2026-03-25 Fix product link
    Updates the product link for LG290P GNSS Flex module w/ IMU
